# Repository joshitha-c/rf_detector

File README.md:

#  Wi-Fi and Bluetooth Signal Tracker

A portable, custom-built RF signal scanner and power detector designed for knowing wireless signals, measuring signal strength and can be used to be safe. Built around the ESP32-C3 microcontroller and the AD8318 logarithmic RF power detector, this device provides real-time visual readings alongside multi-sensory (visual, audible, and tactile) feedback.

---

## Key Features

* **Core Processor:** ESP32-C3-WROOM-02 handling Wi-Fi/Bluetooth scanning, logic, and native USB programming.
* **RF Detection Engine:** AD8318 RF Power Detector module paired with an SMA antenna connector for precise wideband signal measurement.
* **Display:** 2.4-inch SPI TFT LCD (ILI9341) for live graphical signal readouts.
* **UI Controls:** EC11 Rotary Encoder with an integrated push button, expanded over I2C using a PCA9536 GPIO expander to free up MCU pins.
* **Multi-Sensory Alerts:**
  * **RGB LED:** Addressable WS2812B LED (Red = Strong, Yellow = Medium, Green = Weak).
  * **Audio:** Active piezo buzzer providing frequency-pitched sound feedback.
  * **Haptics:** Coin vibration motor driven by a low-side MOSFET.
  * **Flashlight:** Integrated 1W white LED powered directly from the battery line.
* **Power & Charging:**
  * Powered by a standard 3.7V Li-Po/Li-ion single cell.
  * Onboard USB-C port backed by an MCP73831 charger IC (set to 500mA).
  * AP2112K-3.3 (600mA) ultra-low-dropout regulator for stable logic power.
  * Dedicated slide switch for physical battery cut-off.
  * Resistor voltage divider network for monitoring battery percentage in real time.

---
## Bill of Materials (BOM) Summary

| Category | Component | Description / Footprint |
| :--- | :--- | :--- |
| **Microcontroller** | ESP32-C3-WROOM-02 | Main Wi-Fi/BLE MCU (`RF_Module:ESP32-C3-WROOM-02`) |
| **RF Detector** | AD8318 / U.FL Jack | RF Power Detector (`CSP-16` / `U.FL-R-SMT-1`) |
| **Power Management** | MCP73831 & AP2112K-3.3 | Li-Po Charger & 600mA LDO Regulator (`DFN-8` / `SOT-23-5`) |
| **Display** | 2.4" ILI9341 TFT | 320x240 SPI Screen Module Header (`1x14 2.54mm`) |
| **I2C Expander** | PCA9536D | 4-bit GPIO Expander for Encoder (`SOIC-8`) |
| **Input** | EC11 Encoder | Rotary Encoder with Switch (`RotaryEncoder_EC11E`) |
| **Lighting** | WS2812B & 1W White LED | RGB Status LED & Flashlight (`5050 SMD` / `3535 SMD`) |
| **Drivers** | AO3400A / 2N7002 | N-Channel MOSFETs (`SOT-23`) |
| **Passives** | Resistors / Capacitors | Standard 0805 SMD footprints |

## Tools Used

* **Design Software:** KiCad)
## schematics:

## pcb:

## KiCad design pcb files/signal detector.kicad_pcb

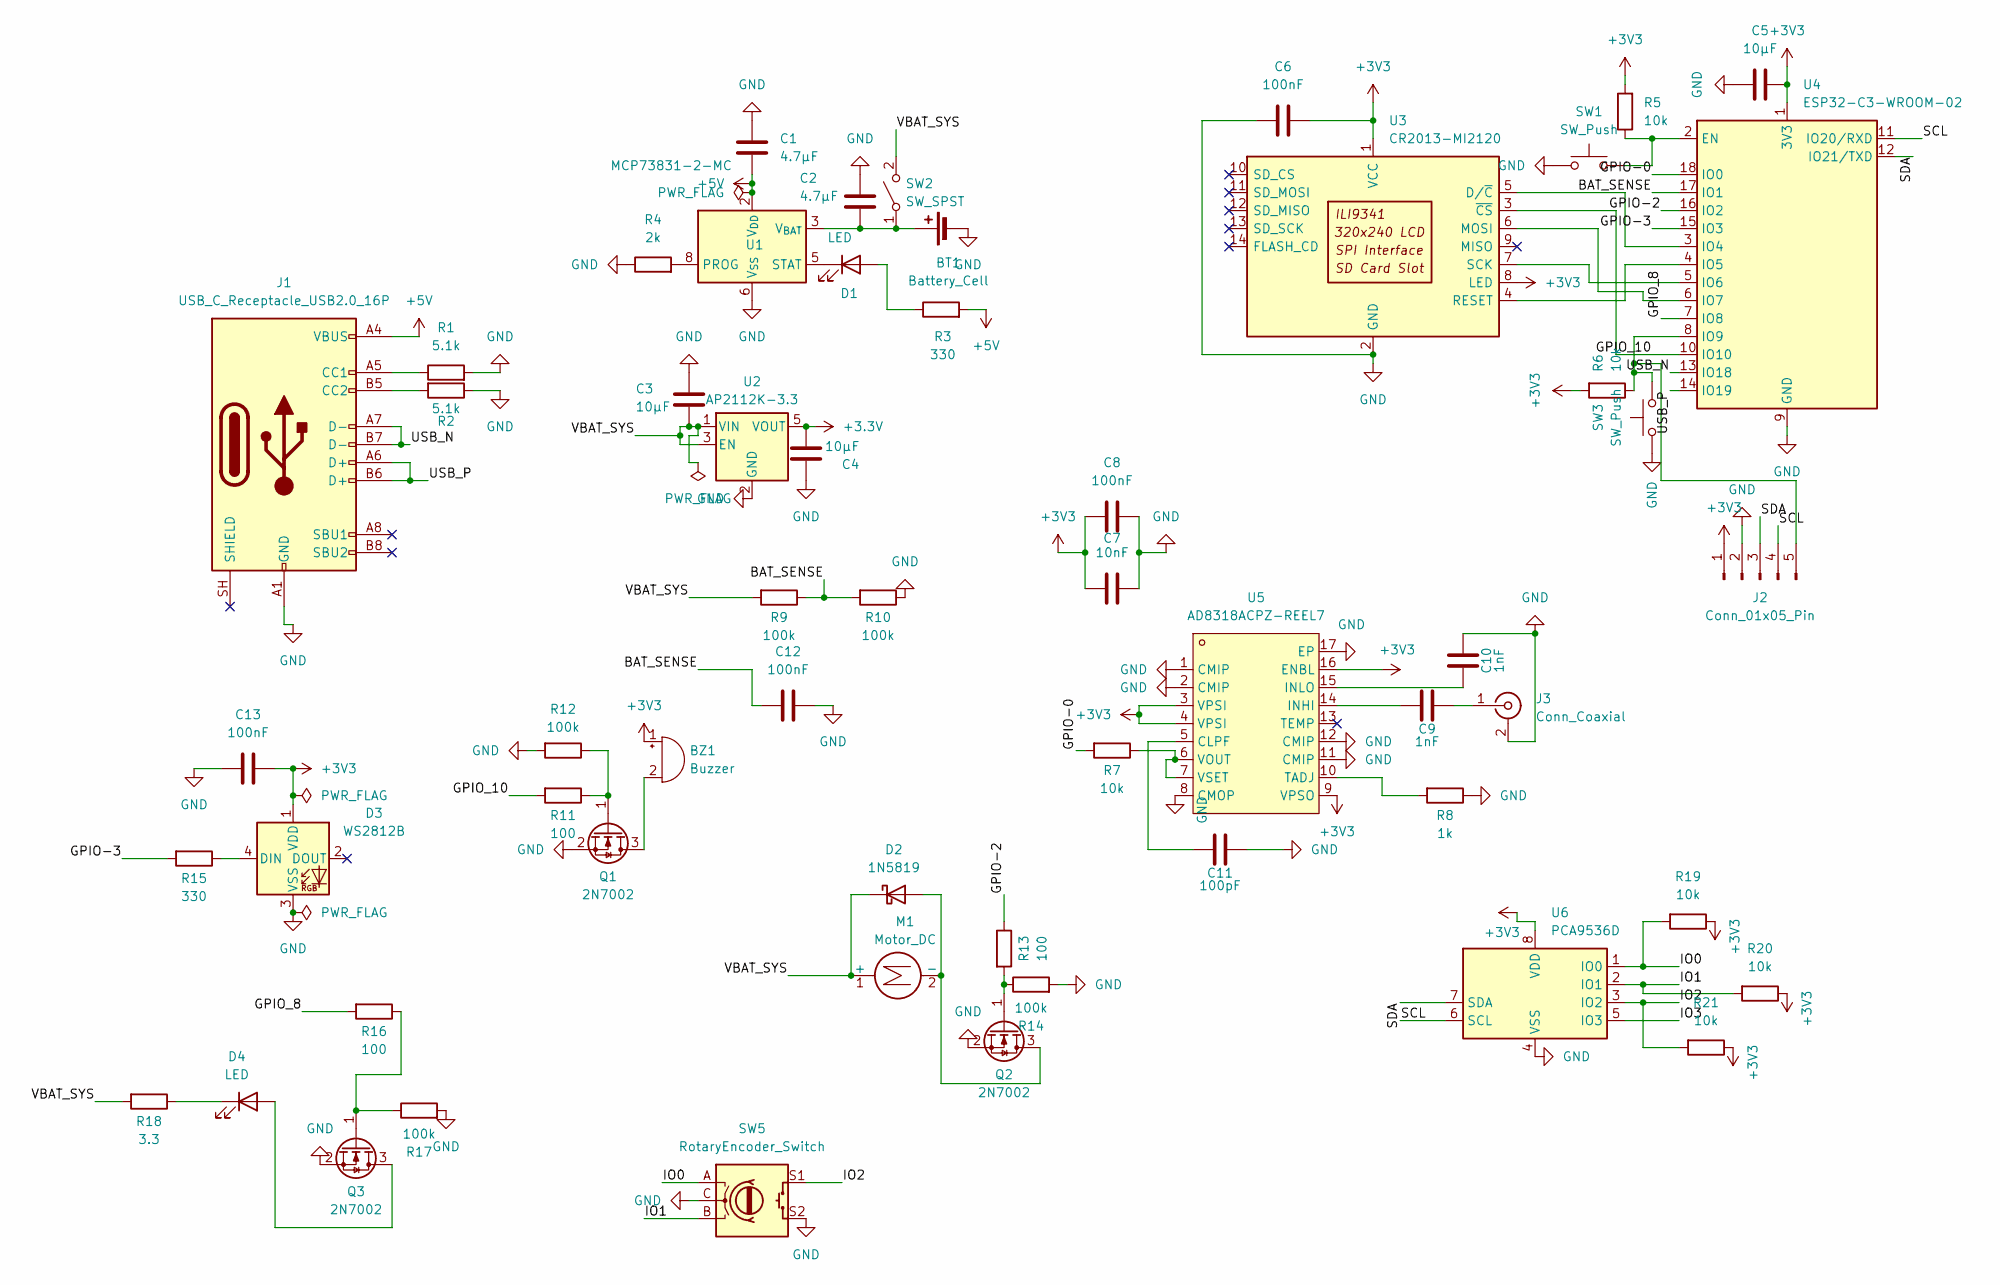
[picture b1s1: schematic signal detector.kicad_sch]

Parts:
BT1: Battery_Cell; JST_PH_B2B-PH-K_1x02_P2.00mm_Vertical
BZ1: Buzzer; Buzzer_12x9.5RM7.6
C1, C2: 4.7µF; C_0805_2012Metric
C3, C4, C5: 10µF; C_0805_2012Metric
C6, C8, C12, C13: 100nF; C_0805_2012Metric
C7: 10nF; C_0805_2012Metric
C9, C10: 1nF; C_0805_2012Metric
C11: 100pF; C_0805_2012Metric
D1: LED; LED_0805_2012Metric
D2: 1N5819; D_DO-41_SOD81_P10.16mm_Horizontal
D3: WS2812B; LED_WS2812B_PLCC4_5.0x5.0mm_P3.2mm
D4: LED; LED_D3.0mm
J1: USB_C_Receptacle_USB2.0_16P; USB_C_Receptacle_HRO_TYPE-C-31-M-12
J2: Conn_01x05_Pin; PinHeader_1x05_P2.54mm_Vertical
J3: Conn_Coaxial; U.FL_Hirose_U.FL-R-SMT-1_Vertical
M1: Motor_DC; R_0805_2012Metric
Q1, Q2, Q3: 2N7002; SOT-23
R1, R2: 5.1k; R_0805_2012Metric
R3, R15: 330; R_0805_2012Metric
R4: 2k; R_0805_2012Metric
R5, R6, R7, R19, R20, R21: 10k; R_0805_2012Metric
R8: 1k; R_0805_2012Metric
R9, R10, R12, R14, R17: 100k; R_0805_2012Metric
R11, R13, R16: 100; R_0805_2012Metric
R18: 3.3; R_0805_2012Metric
SW1, SW3: SW_Push; SW_SPST_PTS645Sx43SMTR92
SW2: SW_SPST; SW_SPST_CK_KMS2xxG
SW5: RotaryEncoder_Switch; RotaryEncoder_Alps_EC11E-Switch_Vertical_H20mm
U1: MCP73831-2-MC; DFN-8-1EP_3x2mm_P0.5mm_EP1.7x1.4mm
U2: AP2112K-3.3; SOT-23-5
U3: CR2013-MI2120
U4: ESP32-C3-WROOM-02
U5: AD8318ACPZ-REEL7; LFCSP-16_L4.0-W4.0-P0.65-BL-EP2.2; MPN AD8318ACPZ-REEL7; LCSC Part C578694
U6: PCA9536D; SOIC-8_3.9x4.9mm_P1.27mm

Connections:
+3.3V: C4.1, U2.5 (VOUT)
+3V3: BZ1.1 (+), C5.1, C6.1, C7.2, C8.2, C13.1, D3.1 (VDD), J2.1, R5.2, R6.2, R19.1, R20.1, R21.1, U3.1 (VCC), U3.8 (LED), U4.1 (3V3), U5.3 (VPSI), U5.4 (VPSI), U5.9 (VPSO), U5.16 (ENBL), U6.8 (VDD)
+5V: C1.1, J1.A4 (VBUS), J1.A9 (VBUS), J1.B4 (VBUS), J1.B9 (VBUS), R3.2, U1.1 (V_{DD}), U1.2 (V_{DD})
/BAT_SENSE: C12.2, R9.1, R10.2, U4.17 (IO1)
/GPIO-0: R7.2, U4.18 (IO0)
/GPIO-2: R13.1, U4.16 (IO2)
/GPIO-3: R15.2, U4.15 (IO3)
/GPIO_8: R16.2, U4.7 (IO8)
/GPIO_10: R11.2, U3.3 (~CS), U4.10 (IO10)
/IO0: R19.2, SW5.A, U6.1 (IO0)
/IO1: R20.2, SW5.B, U6.2 (IO1)
/IO2: R21.2, SW5.S1, U6.3 (IO2)
/IO3: U6.5 (IO3)
/SCL: J2.4, U4.11 (IO20/RXD), U6.6 (SCL)
/SDA: J2.3, U4.12 (IO21/TXD), U6.7 (SDA)
/USB_N: J1.A7 (D-), J1.B7 (D-), U4.13 (IO18)
/USB_P: J1.A6 (D+), J1.B6 (D+), U4.14 (IO19)
/VBAT_SYS: C3.1, D2.1 (K), M1.1 (+), R9.2, R18.2, SW2.2 (B), U2.1 (VIN), U2.3 (EN)
GND: BT1.2 (-), C1.2, C2.2, C3.2, C4.2, C5.2, C6.2, C7.1, C8.1, C10.1, C11.1, C12.1, C13.2, D3.3 (VSS), J1.A1 (GND), J1.A12 (GND), J1.B1 (GND), J1.B12 (GND), J2.2, J3.2 (Ext), Q1.2 (S), Q2.2 (S), Q3.2 (S), R1.2, R2.1, R4.1, R8.1, R10.1, R12.2, R14.2, R17.2, SW1.1, SW3.1, SW5.C, SW5.S2, U1.6 (V_{SS}), U2.2 (GND), U3.2 (GND), U4.9 (GND), U4.19 (GND), U5.1 (CMIP), U5.2 (CMIP), U5.8 (CMOP), U5.11 (CMIP), U5.12 (CMIP), U5.17 (EP), U6.4 (VSS)
unnamed: BT1.1 (+), C2.1, SW2.1 (A), U1.3 (V_{BAT}), U1.4 (V_{BAT})
unnamed: BZ1.2 (-), Q1.3 (D)
unnamed: D1.2 (A), R3.1
unnamed: D1.1 (K), U1.5 (STAT)
unnamed: D2.2 (A), M1.2 (-), Q2.3 (D)
unnamed: D3.4 (DIN), R15.1
unnamed: D4.2 (A), Q3.3 (D)
unnamed: D4.1 (K), R18.1
unnamed: J1.A5 (CC1), R1.1
unnamed: J1.B5 (CC2), R2.2
unnamed: J2.5, R6.1, SW3.2, U4.8 (IO9)
unnamed: C9.1, J3.1 (In)
unnamed: Q1.1 (G), R11.1, R12.1
unnamed: Q2.1 (G), R13.2, R14.1
unnamed: Q3.1 (G), R16.1, R17.1
unnamed: R4.2, U1.8 (PROG)
unnamed: U3.5 (D/~C), U4.3 (IO4)
unnamed: U3.6 (MOSI), U4.6 (IO7)
unnamed: U3.4 (RESET), U4.4 (IO5)
unnamed: U3.7 (SCK), U4.5 (IO6)
unnamed: R5.1, SW1.2, U4.2 (EN)
unnamed: C11.2, U5.5 (CLPF)
unnamed: C9.2, U5.14 (INHI)
unnamed: C10.2, U5.15 (INLO)
unnamed: R8.2, U5.10 (TADJ)
unnamed: R7.1, U5.6 (VOUT), U5.7 (VSET)

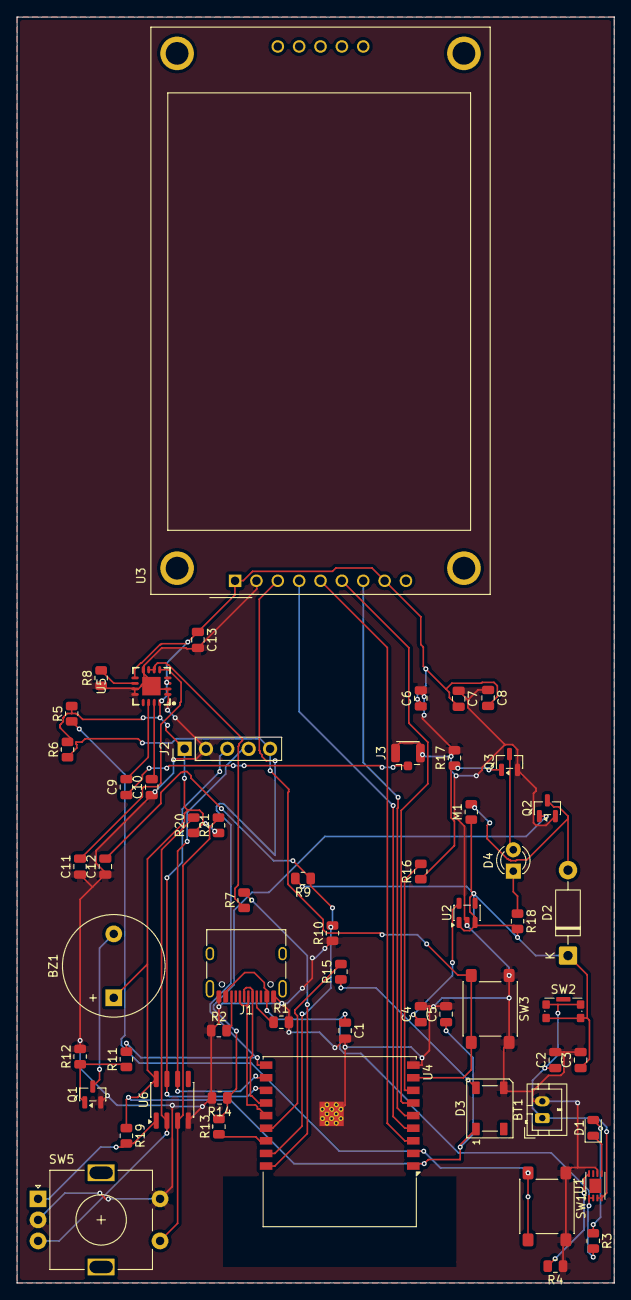
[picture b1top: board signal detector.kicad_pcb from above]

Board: 2 copper layers, 71.0 x 150.5 mm, 57 parts (0 on the bottom side), 44 nets.
